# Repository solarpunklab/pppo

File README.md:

## SOLAR THIEF 
aka Pico Power Plant Oscillator

<!-- PROJECT LOGO -->
<div align="left">

<br />

<br />

</div>

<br />

<!-- TABLE OF CONTENTS -->
<details open>
  <summary style="background-color: #030;">CONTENTS</summary>
  <ul>
    <li><a href="#about">In a nutshell</a></li>
    <li><a href="#description">Description</a>
    <li><a href="#functional">Functional trigger resolution</a>
     <li><a href="#compromises">Compromises</a>  
     <li><a href="#operation">Theory of operation</a>  
      <li><a href="#pcb">PCB, Gerber and BOM</a> 
     <li><a href="#credits">Credits</a>     

  </ul>
</details>

<hr>

## Solar Thief in a nutshell
<p align="justify" id="about">

<ul>
<li> Harvests energy from small solar panels using a simple joule thief boost converter.
<li> Stores energy in common low-cost electrolytic capacitors.
<li> Provides 5V DC power for short intervals.
<li> Harvests in low light conditions
<li> Provides energy in bursts, the interval between bursts is determined by the solar intensity
<li> Powers small remote sensors indefinitely.

</ul><br><br>

<br><br><hr>

<table width=100% bordercolor=#000>
<tr>
<td width=50% align="center">

<td width=50% align="center">

</tr>
<tr>
<td width=50% align="center">

<td width=50% align="center">

</tr>

</table>

<!-------  BACK   --------->
<p align="left" >[ <a href="#readme-top"> back</a> ]</p>

<hr>

## Solar Thief Energy Harvester
<p align="justify" id="description">

This innovative device utilizes a clever joule thief boost converter to efficiently harvest energy, even from the smallest of panels. It stores the collected power in low-cost electrolytic capacitors, making it an economical choice.
<br>
In need of reliable 5V DC power? The Solar Thief has you covered, delivering power in short, consistent intervals. Whether it's a sunny day or overcast, this harvester performs admirably, even in low light conditions. It adapts to the solar intensity, providing energy bursts that ensure your devices stay powered when they need it most.
<br>
Perfect for powering small remote sensors, the Solar Thief Energy Harvester offers a sustainable, off-grid solution. With this device, you can keep your sensors running indefinitely, making it an ideal choice for remote monitoring and off-grid applications.
<!-------  BACK   --------->
<p align="left" >[ <a href="#readme-top"> back</a> ]</p>

<hr>

## Functional trigger resolution
<p align="justify" id="functional">

<ul>
<li> Input voltage is clamped to 24 V (dissipative clamp is fine)
<li> Triggers when Vcap rises over ~ 24V
<li> Resets when Vcap goes below 5V
<li> Has super low leakage
<li> Reset input overrides and resets to idle.
</ul>
<br><br>
<!-------  BACK   --------->
<p align="left" >[ <a href="#readme-top"> back</a> ]</p>

<hr>

## Compromises
<p align="justify" id="compromises">

All electrolytic capacitors have leakage, this leakage is proportional to the applied voltage and total capacitance, it also increases with temperature.
<br>
Our Joule-thief circuit acts as an energy pump, supplying fixed chunks of energy in every cycle,  while boosting the voltage at the same time. What this means is that when the storage capacitor is at a low voltage, the current output of the converter is relatively high, as the capacitor voltage rises, the current decreases, maintaining a constant current x voltage product. The capacitor charges rapidly at the start, but begins slowing as the voltage increases.
Since the energy stored in the capacitor is = ½ CV2, the amount of energy we can store is increased substantially by allowing the capacitor to reach higher charge voltages.
<br>
The compromise is therefore the balance of charging current to leakage current. When the charging current and leakage current become equal, the capacitor voltage no longer rises, and the circuit remains “stuck’ in this state if this equilibrium voltage is lower than the trigger circuit threshold.
It’s tempting to add more capacitance to increase the circuits run-time, but this does have the effect of increasing the amount of input power required for cycling.
<br>
The optimal solution is to size the storage capacitor to the load being driven, keeping the capacitor as small as possible to minimize the parasitic leakage.

<!-------  BACK   --------->
<p align="left" >[ <a href="#readme-top"> back</a> ]</p>

<hr>

## Theory of operation
<p align="justify" id="operation">
<br>

Q3 and common-mode choke LI form a classical joule thief circuit, with two coil windings on the same core. This circuit can operate from as little as 0.6 volts.
When power is applied, current flow through R1 into the base of the transistor starts collector current flowing, this current induces an aiding voltage in the winding connected to the base, which in turn supplies even more base current. This regenerative action continues until the core is fully magnetized and cannot support additional current, when this occurs, the magnetic field begins to collapse, which induces a voltage pulse at Q3’s collector, rising as the transistor stops conducting.
The base-connected winding now reverses polarity, shutting the transistor off even faster, this action continues until the transistor is totally cut off. 
The voltage on the collector rises until a path for L1’s energy develops, which is through D3 and D1 to the storage capacitor, L1 transfers most of it’s energy to the capacitor and the cycle repeats.
The storage capacitor now charges slowly until the trigger circuit fires, turning on the output regulator.
Transistors Q1, Q2 and Q4 form the voltage sensing trigger switch.<br>
The Zener diode D4 begins to conduct once the storage capacitor nears 24 volts, Q2 amplifies this Zener current and feeds a signal to the latch-connected pair Q1 and Q4. These transistors are connected in a way that causes them to latch into a conductive state when either one begins conducting- any current through Q4 causes Q1 to conduct- which feeds back to Q1 - until they are both locked in conduction.
<br><br>

<br><br>

The conduction of Q4 raises the voltage on the emitter, which feeds the voltage divider formed by R6 and R7, the resulting voltage is fed to the ENABLE pin of the LT8606 switching regulator, which has been dormant, consuming almost zero current, the rising voltage turns on the regulator, which is powered by the main storage capacitor via D2. The regulator now outputs a fixed, regulated voltage of either 5 or 3.3 volts, depending on the setting of the jumper P2, which adjusts the ratio of feedback resistance in the regulators feedback loop, consisting of C7, R13 and R14+R12.<br>
Note that power from the joule thief can also continue to flow and assist in powering the circuit via D3.
The additional transistor Q5 allows an external signal to shut down the and reset the system by forcing Q4’s base to ground, which shuts off both the regulator and Q1.
<br><br>
When the capacitor voltage drops near the minimum voltage to keep the regulator working, the voltage on the ENABLE drops below the threshold, shutting down the regulator.
With the load removed, all charging current flows through D1 which causes a reverse bias of Q1, ensuring that the pair Q1-Q4 unlatch and cease conduction.
<br><br>
And the cycle repeats -
<br><br>

<p align="left" >[ <a href="#readme-top"> back</a> ]</p>

<hr>

## PCB / Gerber & BOM
<a href="board/"><p align="justify" id="pcb"></a>

<a href="board/">KiCad project</a>
<!-------  BACK   --------->
<p align="left" >[ <a href="#readme-top"> back</a> ]</p>

<hr>

## Credits
<p align="justify" id="credits">

This project was possible thanks to the wisdom and genius of master <a href="https://www.youtube.com/@leosbagoftricks3732">Leo Fernekes </a> and the generous moral and financial support of  <a href ="https://milieux.concordia.ca">MILIEUX</a> / Concordia University (Montreal).
<br><br>
Circuit design: Leo Fernekes
<br>
PCB / KiCad design: TeZ
<!-------  BACK   --------->
<p align="left" >[ <a href="#readme-top"> back</a> ]</p>

<hr>

## CONTACT
<p align="justify" id="contact">

<a href="mailto:tez@solarpunklab.org">tez@solarpunklab.org
<!-------  BACK   --------->
<p align="left" >[ <a href="#readme-top"> back</a> ]</p>

<hr>

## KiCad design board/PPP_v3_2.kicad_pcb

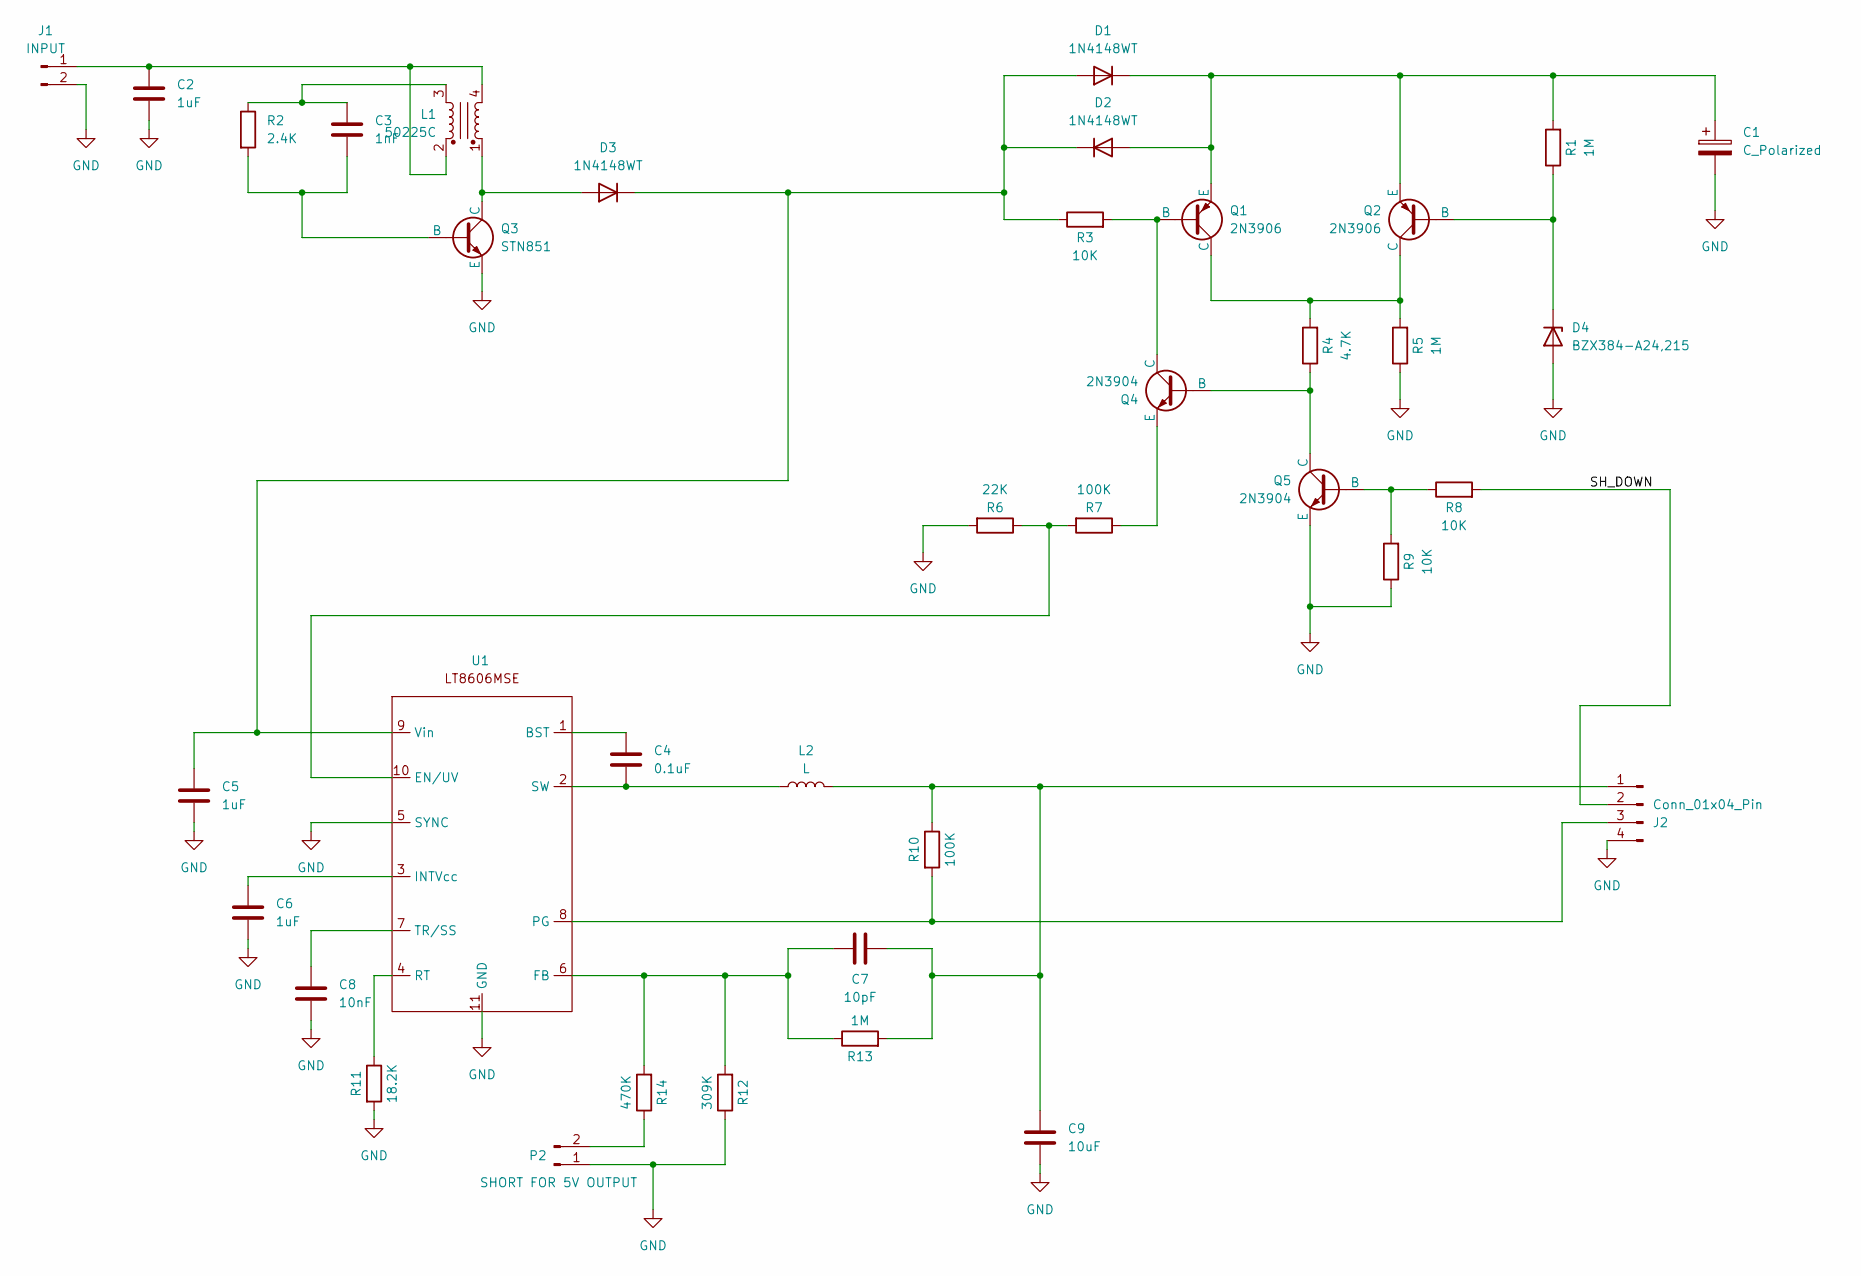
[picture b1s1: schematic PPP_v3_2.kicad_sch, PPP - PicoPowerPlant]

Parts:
C1: C_Polarized; CP_Radial_D25.0mm_P10.00mm_SnapIn
C2, C6: 1uF; C_0805_2012Metric_Pad1.18x1.45mm_HandSolder
C3: 1nF; C_0805_2012Metric_Pad1.18x1.45mm_HandSolder
C4: 0.1uF; C_0805_2012Metric_Pad1.18x1.45mm_HandSolder
C5: 1uF; C_1206_3216Metric_Pad1.33x1.80mm_HandSolder
C7: 10pF; C_0805_2012Metric_Pad1.18x1.45mm_HandSolder
C8: 10nF; C_0805_2012Metric_Pad1.18x1.45mm_HandSolder
C9: 10uF; C_1206_3216Metric_Pad1.33x1.80mm_HandSolder
D1, D2, D3: 1N4148WT; D_SOD-123-1N4148W-TP
D4: BZX384-A24,215; SOT-23-BZX84
J1: INPUT; PinHeader_1x02_P2.54mm_Vertical
J2: Conn_01x04_Pin; PinHeader_1x04_P2.54mm_Vertical
L1: 50225C; L_CMC_50225C
L2: L; L_1210_3225Metric_Pad1.42x2.65mm_HandSolder
P2: SHORT FOR 5V OUTPUT; SolderJumper-2_P1.3mm_Open_RoundedPad1.0x1.5mm
Q1, Q2: 2N3906; SOT-23-MMBT3904
Q3: STN851; SOT-223
Q4, Q5: 2N3904; SOT-23-MMBT3904
R1, R5, R13: 1M; R_0805_2012Metric_Pad1.20x1.40mm_HandSolder
R2: 2.4K; R_0805_2012Metric_Pad1.20x1.40mm_HandSolder
R3, R8, R9: 10K; R_0805_2012Metric_Pad1.20x1.40mm_HandSolder
R4: 4.7K; R_0805_2012Metric_Pad1.20x1.40mm_HandSolder
R6: 22K; R_0805_2012Metric_Pad1.20x1.40mm_HandSolder
R7, R10: 100K; R_0805_2012Metric_Pad1.20x1.40mm_HandSolder
R11: 18.2K; R_0805_2012Metric_Pad1.20x1.40mm_HandSolder
R12: 309K; R_0805_2012Metric_Pad1.20x1.40mm_HandSolder
R14: 470K; R_0805_2012Metric_Pad1.20x1.40mm_HandSolder
U1: LT8606-MSOP-10-3x3mm

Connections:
/SH_DOWN: J2.2, R8.2
GND: C1.2, C2.2, C5.2, C6.2, C8.2, C9.2, D4.2 (A), J1.2, J2.4, P2.1, Q3.3 (E), Q5.3 (E), R5.1, R6.2, R9.1, R11.2, R12.1, U1.5 (SYNC), U1.11 (GND)
unnamed: C3.1, L1.3, R2.1
unnamed: C5.1, D1.2 (A), D2.1 (K), D3.1 (K), R3.1, U1.9 (Vin)
unnamed: C1.1, D1.1 (K), D2.2 (A), Q1.3 (E), Q2.3 (E), R1.2
unnamed: D3.2 (A), L1.1, Q3.2 (C)
unnamed: D4.1 (K), Q2.2 (B), R1.1
unnamed: C2.1, J1.1, L1.2, L1.4
unnamed: C7.2, C9.1, J2.1, L2.2, R10.1, R13.2
unnamed: J2.3, R10.2, U1.8 (PG)
unnamed: P2.2, R14.1
unnamed: Q1.2 (B), Q4.1 (C), R3.2
unnamed: Q1.1 (C), Q2.1 (C), R4.2, R5.2
unnamed: C3.2, Q3.1 (B), R2.2
unnamed: Q4.2 (B), Q5.1 (C), R4.1
unnamed: Q4.3 (E), R7.1
unnamed: Q5.2 (B), R8.1, R9.2
unnamed: C4.1, U1.1 (BST)
unnamed: R6.1, R7.2, U1.10 (EN/UV)
unnamed: C7.1, R12.2, R13.1, R14.2, U1.6 (FB)
unnamed: C6.1, U1.3 (INTVcc)
unnamed: R11.1, U1.4 (RT)
unnamed: C4.2, L2.1, U1.2 (SW)
unnamed: C8.1, U1.7 (TR/SS)

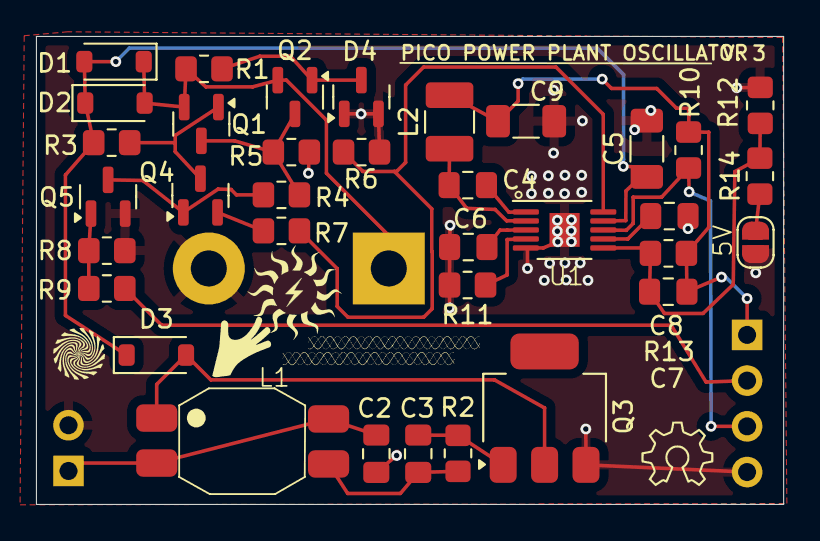
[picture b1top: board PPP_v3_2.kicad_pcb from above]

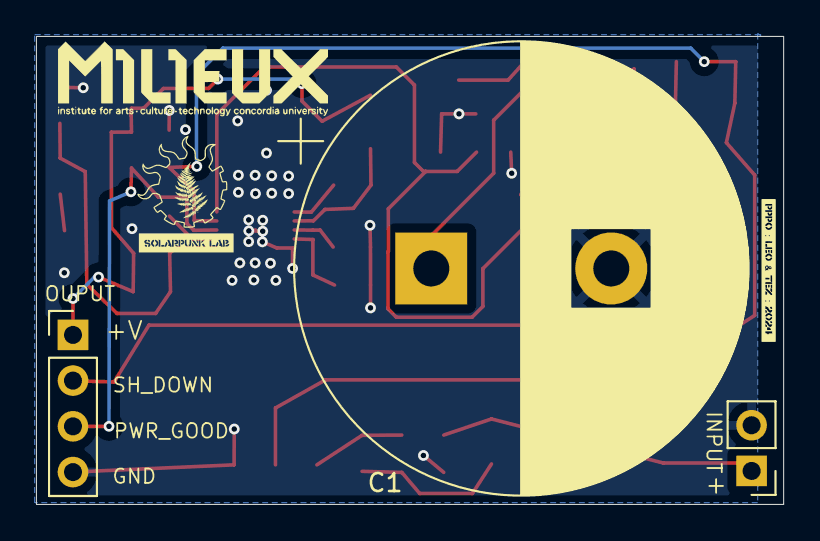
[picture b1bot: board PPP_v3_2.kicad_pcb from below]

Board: 2 copper layers, 41.5 x 26.0 mm, 38 parts (3 on the bottom side), 24 nets.

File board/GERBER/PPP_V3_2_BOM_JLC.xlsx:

PPP_V3_BOM
PART DESCRIPTION | DESIGNATOR | FOOTPRINT | JLCPCB PART (opt.) | note
IC REG BUCK ADJ 350MA 10MSOP | U1 | Package_SO:LT8606-MSOP-10-3x3mm
DIODE, SMALL SIGNAL | D1,D2,D3 | Diode_SMD:D_SOD-123-1N4148W-TP
DIODE ZENER 24V | D4 | Package_TO_SOT_SMD:SOT-23-BZX84
Transistor, NPN | Q3 | Package_TO_SOT_SMD:SOT-223
Transistor, NPN | Q4,Q5 | Package_TO_SOT_SMD:SOT-23-MMBT3904
Transistor, PNP | Q1,Q2 | Package_TO_SOT_SMD:SOT-23-MMBT3904
Common Mode Choke | L1 | Inductor_SMD:L_CMC_50225C
10 µH Unshielded, Wirewound Inductor 450 mA 390mOhm | L2 | Inductor_SMD:L_1210_3225Metric_Pad1.42x2.65mm_HandSolder
Capacitor, Ceramic, 1 uF, 16 Volt X7R | C2,C6 | Capacitor_SMD:C_0805_2012Metric_Pad1.18x1.45mm_HandSolder
Capacitor, Ceramic, 1 uF, 50 Volt X7R | C5 | Capacitor_SMD:C_1206_3216Metric_Pad1.33x1.80mm_HandSolder
Capacitor, Ceramic, 10 uF, 50 Volt X7R | C9 | Capacitor_SMD:C_1206_3216Metric_Pad1.33x1.80mm_HandSolder
Capacitor, Ceramic, 1 nF, 50 Volt X7R | C3 | Capacitor_SMD:C_0805_2012Metric_Pad1.18x1.45mm_HandSolder
Capacitor, Ceramic, 10 nF, 50 Volt X7R | C8 | Capacitor_SMD:C_0805_2012Metric_Pad1.18x1.45mm_HandSolder
Capacitor, Ceramic, 0.1 uF, 50 Volt X7R | C4 | Capacitor_SMD:C_0805_2012Metric_Pad1.18x1.45mm_HandSolder
Capacitor, Ceramic, 10 pF, 50 Volt X7R | C7 | Capacitor_SMD:C_0805_2012Metric_Pad1.18x1.45mm_HandSolder
Resistor, 1M ohms, 1% | R1,R5,R13 | Resistor_SMD:R_0805_2012Metric_Pad1.20x1.40mm_HandSolder
Resistor, 309K ohms, 1% | R12 | Resistor_SMD:R_0805_2012Metric_Pad1.20x1.40mm_HandSolder
Resistor, 18.2K ohms, 1% | R11 | Resistor_SMD:R_0805_2012Metric_Pad1.20x1.40mm_HandSolder
Resistor, 100K ohms, 5% | R7, R10 | Resistor_SMD:R_0805_2012Metric_Pad1.20x1.40mm_HandSolder
Resistor, 10K ohms, 5% | R3, R8, R9 | Resistor_SMD:R_0805_2012Metric_Pad1.20x1.40mm_HandSolder
Resistor, 4.7K ohms, 5% | R4 | Resistor_SMD:R_0805_2012Metric_Pad1.20x1.40mm_HandSolder
Resistor, 22K ohms, 5% | R6 | Resistor_SMD:R_0805_2012Metric_Pad1.20x1.40mm_HandSolder
Resistor, 2.4K ohms, 5% | R2 | Resistor_SMD:R_0805_2012Metric_Pad1.20x1.40mm_HandSolder
Resistor, 470K ohms, 1% | R14 | Resistor_SMD:R_0805_2012Metric_Pad1.20x1.40mm_HandSolder
Capacitor, Electrolytic, 4700 uF, 35Volt | C1 | Capacitor_THT:CP_Radial_D25.0mm_P10.00mm_SnapIn |  | THT

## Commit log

2025-01-23 readme update
